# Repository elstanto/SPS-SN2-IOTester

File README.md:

# SPS-SN2-IOTester
IO Tester Board for SPS SN2 electronics upgrade.

Designed using Kicad v5.

There are PDF copies of the schematic and PCB in the PDF folder.

#### Renders

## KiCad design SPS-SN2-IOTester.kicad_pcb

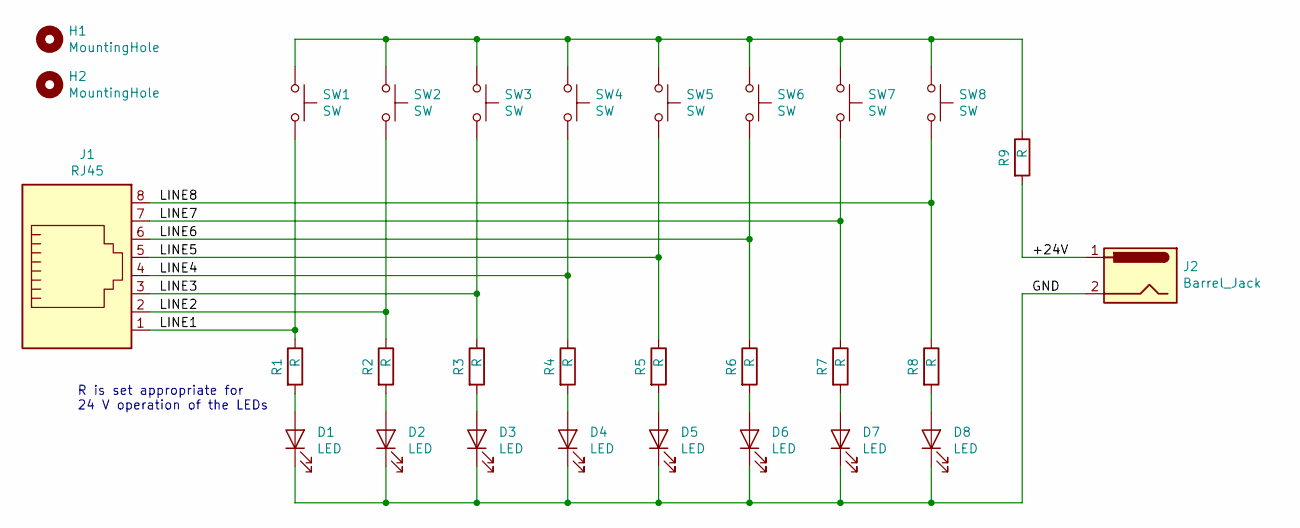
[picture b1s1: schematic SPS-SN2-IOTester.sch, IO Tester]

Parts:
D1, D2, D3, D4, D5, D6, D7, D8: LED; LED_D3.0mm
H1, H2: MountingHole; MountingHole_2.2mm_M2
J1: RJ45; TE_1-406525-1
J2: Barrel_Jack; BarrelJack_Horizontal
R1, R2, R3, R4, R5, R6, R7, R8, R9: R; R_Axial_DIN0207_L6.3mm_D2.5mm_P7.62mm_Horizontal
SW1, SW2, SW3, SW4, SW5, SW6, SW7, SW8: SW; SW_PUSH_6mm_H17mm

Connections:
/+24V: J2.1, R9.2
/GND: D1.1 (K), D2.1 (K), D3.1 (K), D4.1 (K), D5.1 (K), D6.1 (K), D7.1 (K), D8.1 (K), J2.2
/LINE1: J1.1, R1.1, SW1.2
/LINE2: J1.2, R2.1, SW2.2
/LINE3: J1.3, R3.1, SW3.2
/LINE4: J1.4, R4.1, SW4.2
/LINE5: J1.5, R5.1, SW5.2
/LINE6: J1.6, R6.1, SW6.2
/LINE7: J1.7, R7.1, SW7.2
/LINE8: J1.8, R8.1, SW8.2
unnamed: D1.2 (A), R1.2
unnamed: D2.2 (A), R2.2
unnamed: D3.2 (A), R3.2
unnamed: D4.2 (A), R4.2
unnamed: D5.2 (A), R5.2
unnamed: D6.2 (A), R6.2
unnamed: D7.2 (A), R7.2
unnamed: D8.2 (A), R8.2
unnamed: R9.1, SW1.1, SW2.1, SW3.1, SW4.1, SW5.1, SW6.1, SW7.1, SW8.1

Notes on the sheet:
R is set appropriate for 24 V operation of the LEDs

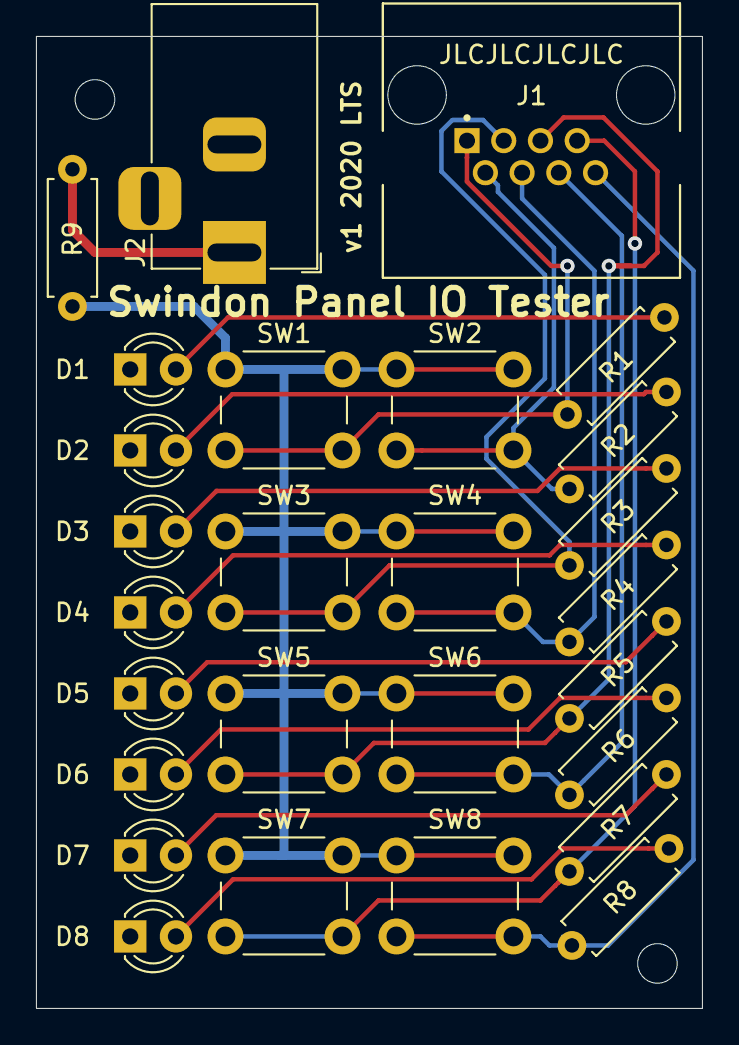
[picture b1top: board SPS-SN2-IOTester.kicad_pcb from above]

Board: 2 copper layers, 37.0 x 54.0 mm, 29 parts (0 on the bottom side), 19 nets.

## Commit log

2019-12-26 initial
2019-12-26 v1 ready
2019-12-26 fixed image links in readme
2019-12-26 added schematic annotation
2019-12-29 added DC barrel jack and moved resistors
2019-12-29 swapped buttons and LEDs for enclosure versions
2020-01-04 Latest version with mounting holes
2020-01-05 Redesigned circuit to prevent switches blowing LEDs
